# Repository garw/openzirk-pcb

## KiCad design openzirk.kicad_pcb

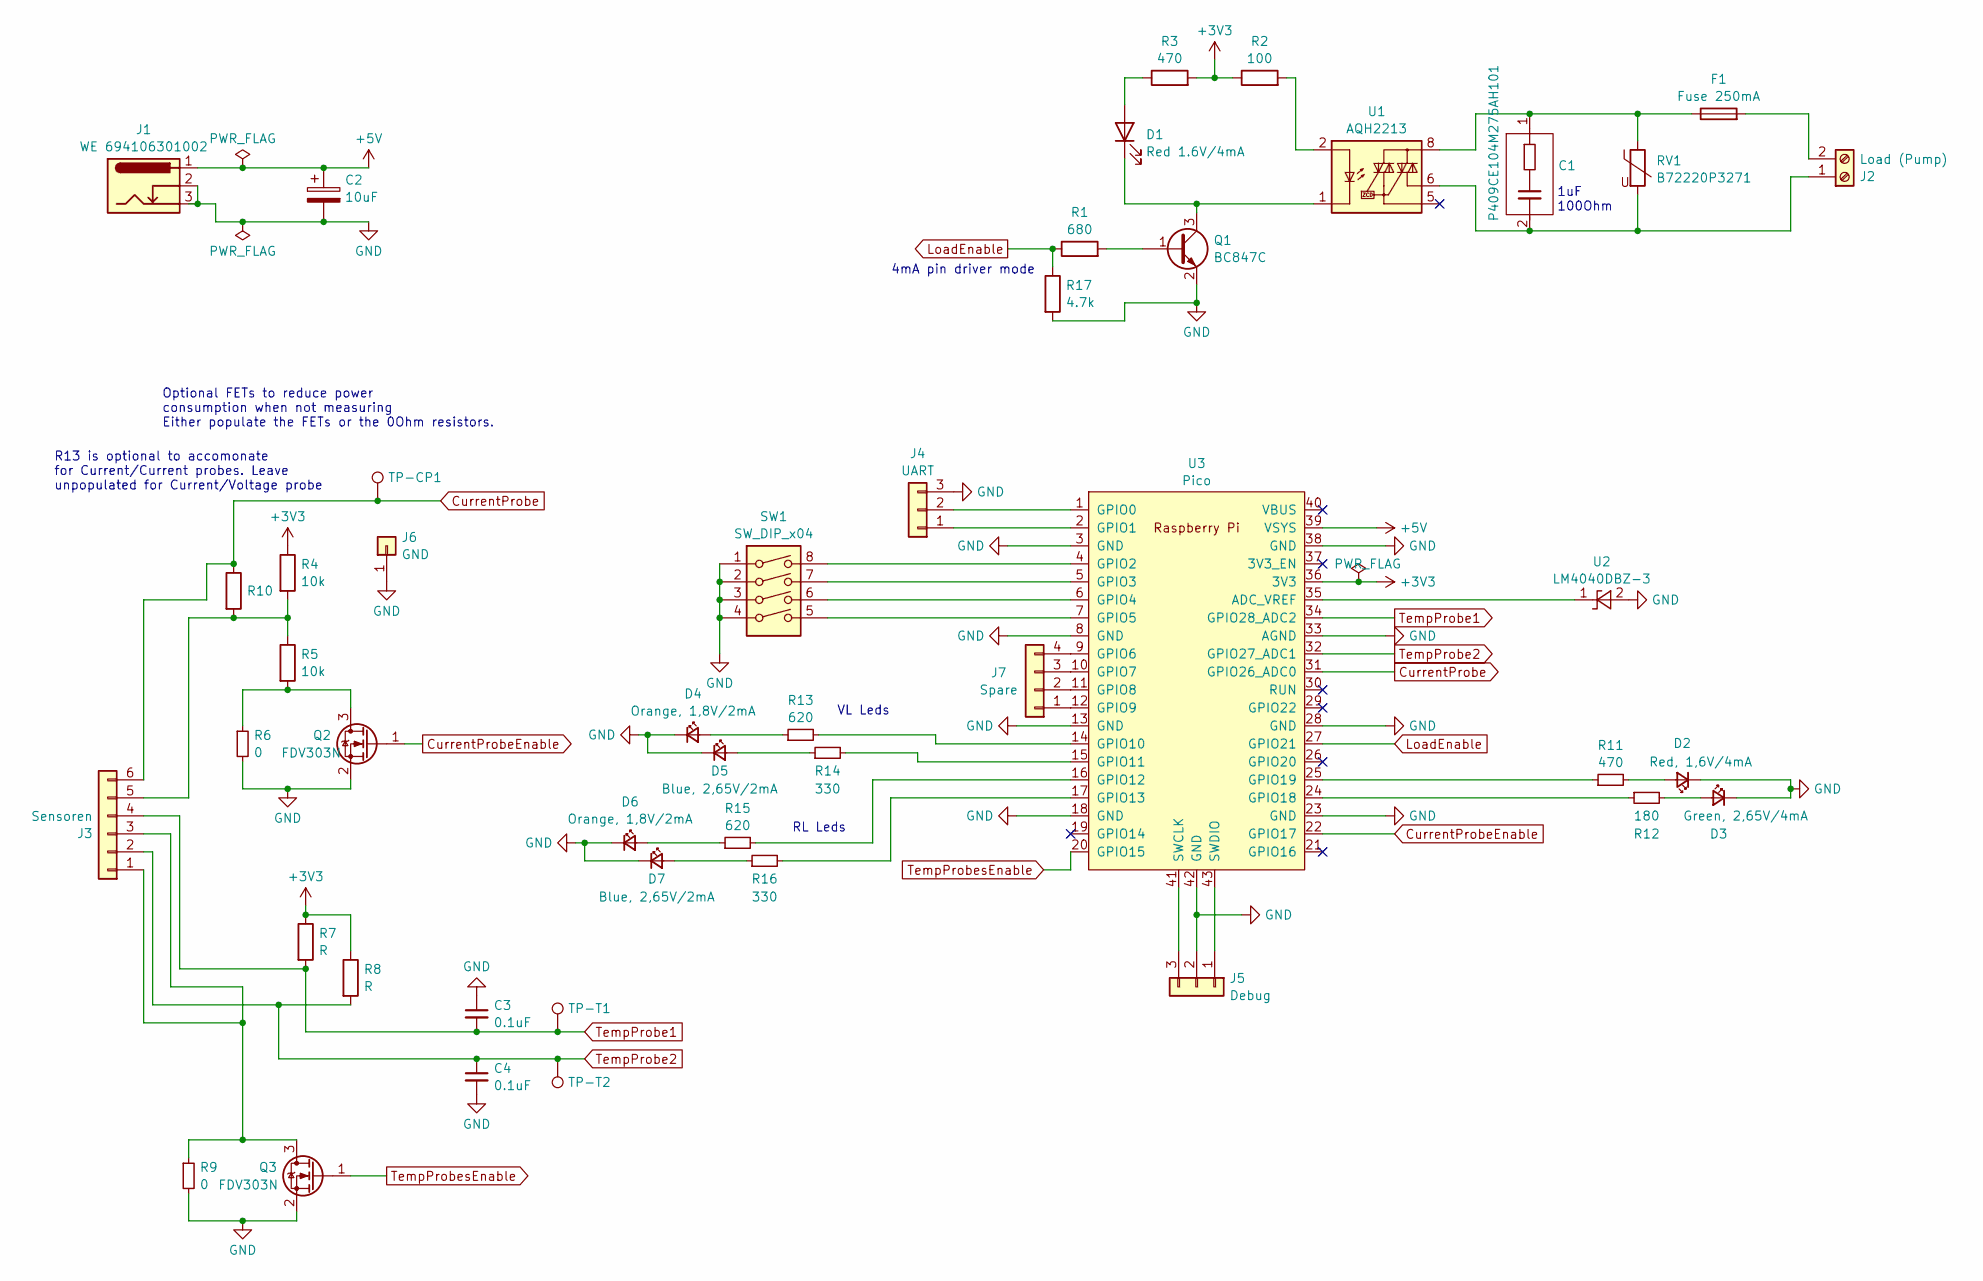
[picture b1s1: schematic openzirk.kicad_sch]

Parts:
C1: P409CE104M275AH101; P409CE104M250AH101
C2: 10uF; CP_Radial_D5.0mm_P2.00mm
C3, C4: 0.1uF; C_0805_2012Metric
D1: Red 1.6V/4mA; LED_0805_2012Metric
D2: Red, 1,6V/4mA; LED_0805_2012Metric
D3: Green, 2,65V/4mA; LED_0805_2012Metric
D4, D6: Orange, 1,8V/2mA; LED_0805_2012Metric
D5, D7: Blue, 2,65V/2mA; LED_0805_2012Metric
F1: Fuse 250mA; 64600001223
J1: WE 694106301002; 694106301002_1
J2: Load (Pump); 1667750000
J3: Sensoren; SHDR6W90P0X350_1X6_2160X1000X1255P
J4: UART; PinHeader_1x03_P2.54mm_Vertical
J5: Debug; PinHeader_1x03_P2.54mm_Vertical
J6: GND; PinHeader_1x01_P2.54mm_Vertical
J7: Spare; PinHeader_1x04_P2.54mm_Vertical
Q1: BC847C; SOT-23
Q2, Q3: FDV303N; SOT-23
R1: 680; R_0805_2012Metric
R2: 100; R_0805_2012Metric
R3, R11: 470; R_0805_2012Metric
R4, R5: 10k; R_0805_2012Metric
R6, R9: 0; R_0805_2012Metric
R7, R8: R; R_0805_2012Metric
R10: R_0805_2012Metric
R12: 180; R_0805_2012Metric
R13, R15: 620; R_0805_2012Metric
R14, R16: 330; R_0805_2012Metric
R17: 4.7k; R_0805_2012Metric
RV1: B72220P3271; RV_Disc_D21.5mm_W7.1mm_P10mm
SW1: SW_DIP_x04; SW_DIP_SPSTx04_Slide_Omron_A6S-410x_W8.9mm_P2.54mm
TP-CP1: TestPoint_Pad_D1.5mm
TP-T1, TP-T2: TestPoint; TestPoint_Pad_D1.5mm
U1: AQH2213; DIP-8-N7_W7.62mm
U2: LM4040DBZ-3; SOT-23
U3: Pico; RPi_Pico_SMD_TH

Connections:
+3V3: R2.1, R3.2, R4.1, R7.1, R8.1, U3.36 (3V3)
+5V: C2.1, J1.1, U3.39 (VSYS)
CurrentProbe: J3.6, R10.1, TP-CP1.1, U3.31 (GPIO26_ADC0)
CurrentProbeEnable: Q2.1 (G), U3.22 (GPIO17)
GND: C2.2, C3.1, C4.2, D2.1 (K), D3.1 (K), D4.1 (K), D5.1 (K), D6.1 (K), D7.1 (K), J1.2, J1.3, J4.3, J5.2, J6.1, Q1.2 (E), Q2.2 (S), Q3.2 (S), R6.2, R9.2, R17.2, SW1.1, SW1.2, SW1.3, SW1.4, U2.2 (A), U3.3 (GND), U3.8 (GND), U3.13 (GND), U3.18 (GND), U3.23 (GND), U3.28 (GND), U3.33 (AGND), U3.38 (GND), U3.42 (GND)
LoadEnable: R1.1, R17.1, U3.27 (GPIO21)
unnamed: C1.1, F1.1, RV1.1, U1.8
unnamed: D1.2 (A), R3.1
unnamed: D1.1 (K), Q1.3 (C), U1.1, U1.3, U1.4
unnamed: D2.2 (A), R11.2
unnamed: D3.2 (A), R12.2
unnamed: D4.2 (A), R13.1
unnamed: D5.2 (A), R14.1
unnamed: D6.2 (A), R15.1
unnamed: D7.2 (A), R16.1
unnamed: C1.2, J2.1, RV1.2, U1.6
unnamed: F1.2, J2.2
unnamed: J3.1, J3.3, Q3.3 (D), R9.1
unnamed: J3.5, R4.2, R5.1, R10.2
unnamed: J4.1, U3.2 (GPIO1)
unnamed: J4.2, U3.1 (GPIO0)
unnamed: J5.1, U3.43 (SWDIO)
unnamed: J5.3, U3.41 (SWCLK)
unnamed: J7.1, U3.12 (GPIO9)
unnamed: J7.2, U3.11 (GPIO8)
unnamed: J7.3, U3.10 (GPIO7)
unnamed: J7.4, U3.9 (GPIO6)
unnamed: Q1.1 (B), R1.2
unnamed: Q2.3 (D), R5.2, R6.1
unnamed: R2.2, U1.2
unnamed: U2.1 (K), U3.35 (ADC_VREF)
unnamed: SW1.8, U3.4 (GPIO2)
unnamed: SW1.7, U3.5 (GPIO3)
unnamed: SW1.6, U3.6 (GPIO4)
unnamed: SW1.5, U3.7 (GPIO5)
unnamed: R13.2, U3.14 (GPIO10)
unnamed: R14.2, U3.15 (GPIO11)
unnamed: R15.2, U3.16 (GPIO12)
unnamed: R16.2, U3.17 (GPIO13)
unnamed: R12.1, U3.24 (GPIO18)
unnamed: R11.1, U3.25 (GPIO19)
TempProbe1: C3.2, J3.4, R7.2, TP-T1.1, U3.34 (GPIO28_ADC2)
TempProbe2: C4.1, J3.2, R8.2, TP-T2.1, U3.32 (GPIO27_ADC1)
TempProbesEnable: Q3.1 (G), U3.20 (GPIO15)

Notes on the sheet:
1uF 100Ohm
VL Leds
RL Leds
4mA pin driver mode
Optional FETs to reduce power consumption when not measuring Either populate the FETs or the 0Ohm resistors.
R13 is optional to accomonate for Current/Current probes. Leave unpopulated for Current/Voltage probe

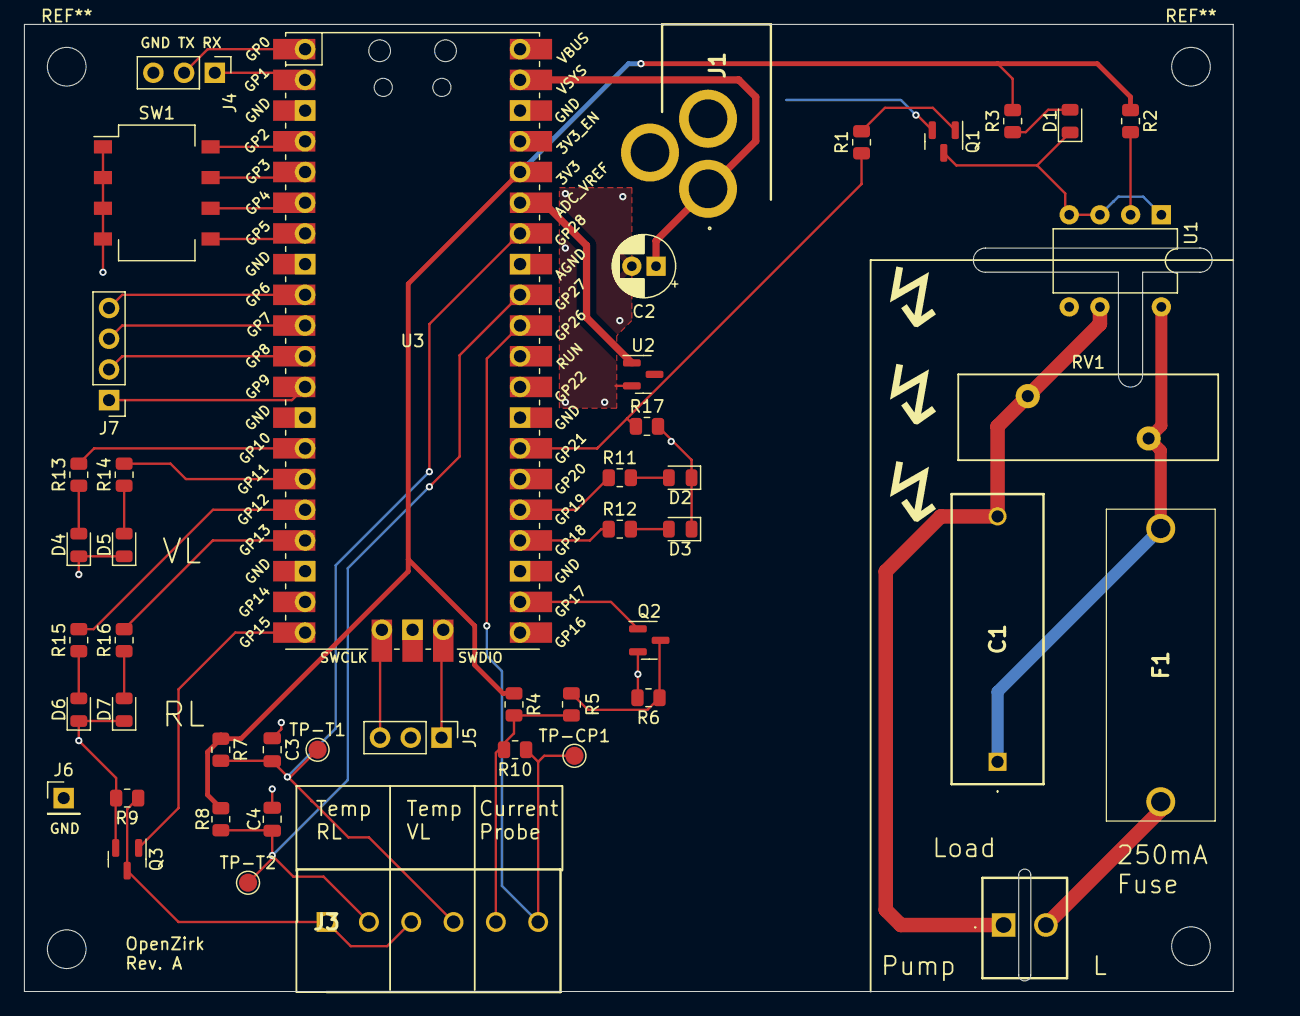
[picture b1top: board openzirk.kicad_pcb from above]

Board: 2 copper layers, 103.5 x 80.0 mm, 47 parts (0 on the bottom side), 44 nets.

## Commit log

2024-01-25 Initial Commit
    OpenZirk PCB Rev A.
